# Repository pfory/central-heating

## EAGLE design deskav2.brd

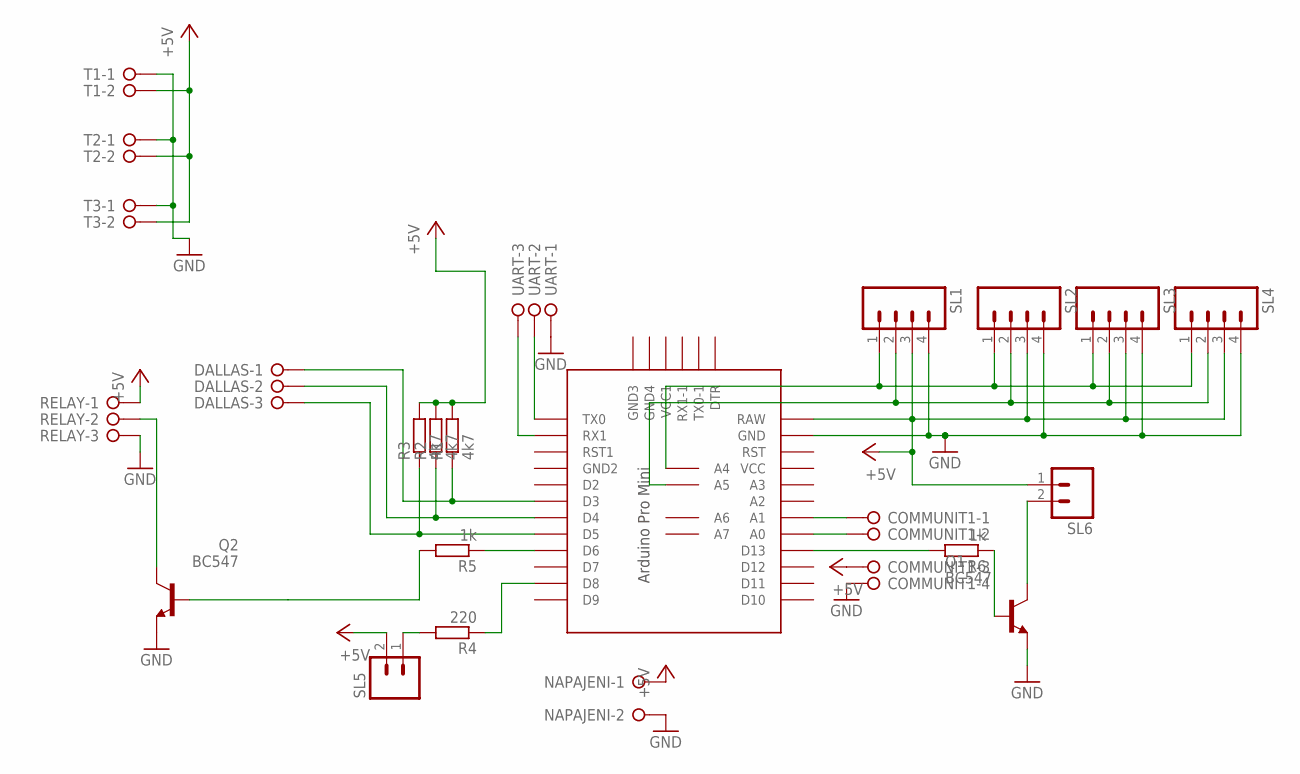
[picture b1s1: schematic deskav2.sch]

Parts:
COMMUNIT1: W237-04P; W237-4P
DALLAS: W237-3E
NAPAJENI: W237-02P; W237-132
Q1, Q2: BC547; TO92
R1, R2, R3: 4k7; 0207/7
R4: 220; 0207/7
R5, R6: 1k; 0207/7
RELAY: W237-3E
SL1, SL2, SL3, SL4: M04; 04P
SL5, SL6: M02; 02P
T1, T2, T3: W237-02P; W237-132
U$1: PRO-MINI-2
UART: W237-3E

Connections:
+5V: COMMUNIT1.3, NAPAJENI.1, R1.2, R2.2, R3.2, RELAY.1, SL1.3, SL2.3, SL3.3, SL4.3, SL5.2, SL6.1, T1.2, T2.2, T3.2, U$1.RAW
GND: COMMUNIT1.4, NAPAJENI.2, Q1.1 (E), Q2.1 (E), RELAY.3, SL1.4, SL2.4, SL3.4, SL4.4, T1.1, T2.1, T3.1, U$1.GND, UART.1
unnamed: DALLAS.2, R2.1, U$1.D4
unnamed: DALLAS.3, R3.1, U$1.D5
unnamed: R5.1, U$1.D6
unnamed: R4.1, U$1.D8
unnamed: R4.2, SL5.1
unnamed: Q1.2 (B), R6.1
unnamed: COMMUNIT1.1, U$1.A1
unnamed: U$1.TX0, UART.2
unnamed: U$1.RX1, UART.3
unnamed: SL1.1, SL2.1, SL3.1, SL4.1, U$1.A4
unnamed: SL1.2, SL2.2, SL3.2, SL4.2, U$1.A5
unnamed: Q2.2 (B), R5.2
unnamed: Q2.3 (C), RELAY.2
unnamed: Q1.3 (C), SL6.2
unnamed: R6.2, U$1.D13
unnamed: COMMUNIT1.2, U$1.A0
unnamed: DALLAS.1, R1.1, U$1.D3

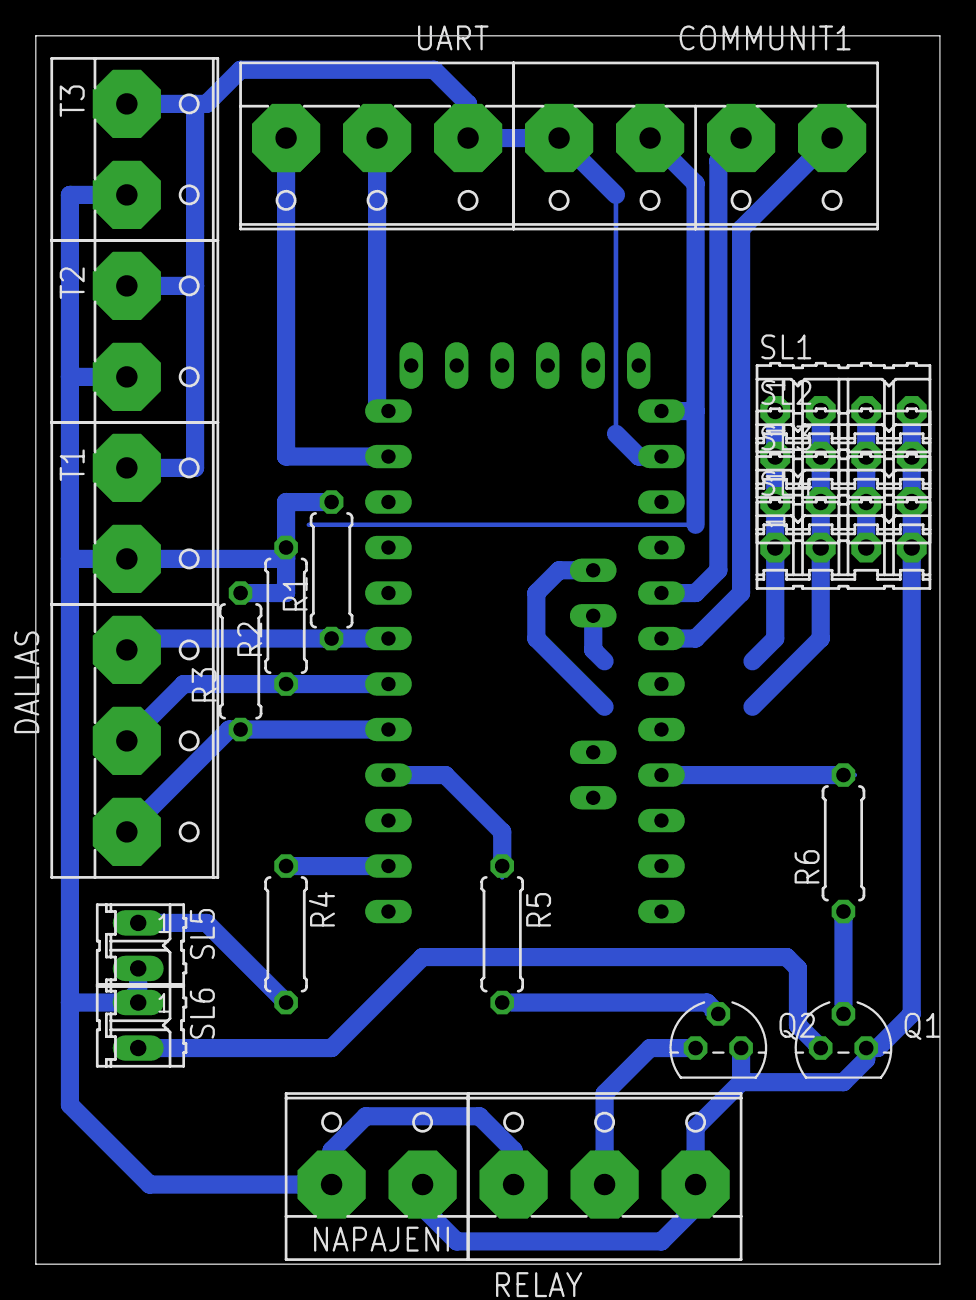
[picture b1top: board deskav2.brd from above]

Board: 2 copper layers, 50.5 x 68.6 mm, 23 parts (0 on the bottom side), 19 nets.

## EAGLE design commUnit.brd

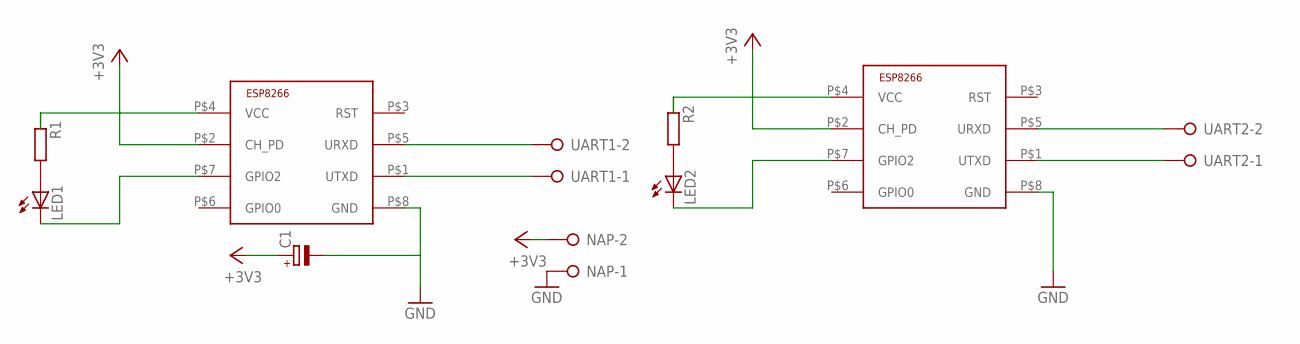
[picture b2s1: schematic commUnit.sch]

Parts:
C1: CPOL-EUE3.5-10; E3,5-10
LED1, LED2: LED3MM
NAP: W237-02P; W237-132
R1, R2: R-EU_0207/10; 0207/10
U$1, U$2: ESP8266-01; ESP-01
UART1, UART2: W237-02P; W237-132

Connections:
+3V3: C1.+, NAP.2, R1.1, R2.1, U$1.P$2 (CH_PD), U$1.P$4 (VCC), U$2.P$2 (CH_PD), U$2.P$4 (VCC)
GND: C1.-, NAP.1, U$1.P$8 (GND), U$2.P$8 (GND)
unnamed: LED1.A, R1.2
unnamed: LED1.K (C), U$1.P$7 (GPIO2)
unnamed: U$1.P$5 (URXD), UART1.2
unnamed: U$1.P$1 (UTXD), UART1.1
unnamed: U$2.P$5 (URXD), UART2.2
unnamed: LED2.A, R2.2
unnamed: LED2.K (C), U$2.P$7 (GPIO2)
unnamed: U$2.P$1 (UTXD), UART2.1

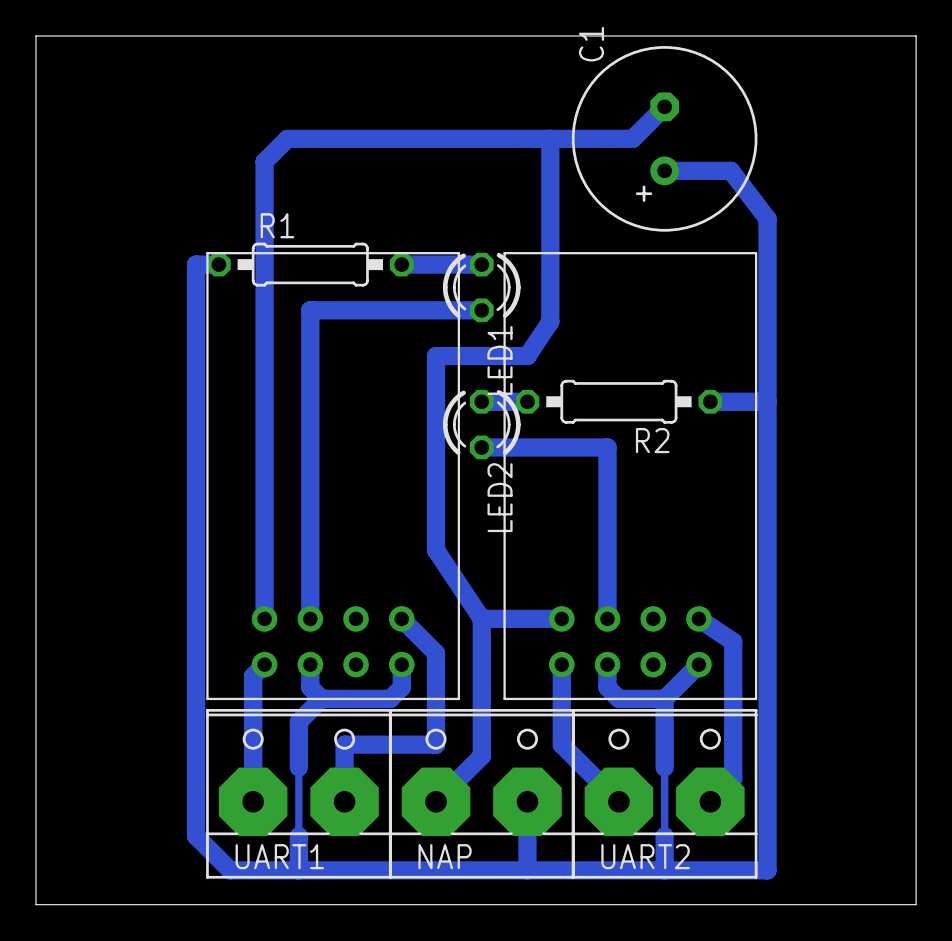
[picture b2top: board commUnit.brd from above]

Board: 2 copper layers, 48.9 x 48.3 mm, 10 parts (0 on the bottom side), 10 nets.

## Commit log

2015-11-02 initial
2015-11-03 v0.1
2015-11-09 doplněn popis.txt
2015-11-09 ulozit
2015-11-18 funkcni spinani rele
2015-11-23 v0.2
2015-11-26 pridano ovladani rele
2015-12-01 doplněno uspořádání svorkovnice
2015-12-01 nespíná relé
2015-12-02 + nastavení teplot - nastavení relé
2015-12-03 + odesilani teplot z cidel radiatoru
2015-12-03 + piny
2015-12-04 +popis klavesnice
2015-12-07 +add
2016-01-02 pred konverzi na arduino
2016-01-03 přidána podpora Arduino
2016-01-03 +dallas test
2016-01-08 změny v zapojení pro Arduino
2016-01-15 doplnění popisu signalizační jednotky
2016-01-15 +nacitani teploty pres I2C
2016-01-15 +comunitation with solar unit via I2C
2016-01-16 +beeper
2016-01-18 -code for ESP8266
2016-03-30 +arduino schema
2016-04-15 +dps
2016-04-20 +autoconnect
2016-04-25 zmeny
2016-04-26 uprava desky, prida konektor pro napajeni
2016-04-26 dokreslen DPS
2016-04-27 +upraveny DPS DPS objednany 27.4.2016
2016-05-04 +deska v2
2016-05-18 v0,51 - reset z GUI
2016-05-25 v0.6 + reconnect each 10 minutes
2016-07-26 pi on chata
2016-10-24 v073
2016-10-25 aktualizace dokumentace
2016-11-03 pridan regex pro rozpoznani zapornych teplot
2016-11-03 opravena chyba se zápornými teplotami
2016-12-26 v0,6
2016-12-27 upravy
2016-12-28 změna pinu
2016-12-31 prvni verze commUnit v c
2017-01-04 HB=12 po bootu
2017-01-18 +beep
2017-09-12 novy bootloader
2017-09-12 optiboot bootloader
2018-06-15 uprava HB sysntaxe
2018-08-27 v0.92
2018-08-28 oprava HB
2018-11-01 v1.0 - wifimaneger bez zaseku
2018-11-01 v1.0 final
2018-11-01 +bin
2019-10-01 zmena na 45/40 spad
